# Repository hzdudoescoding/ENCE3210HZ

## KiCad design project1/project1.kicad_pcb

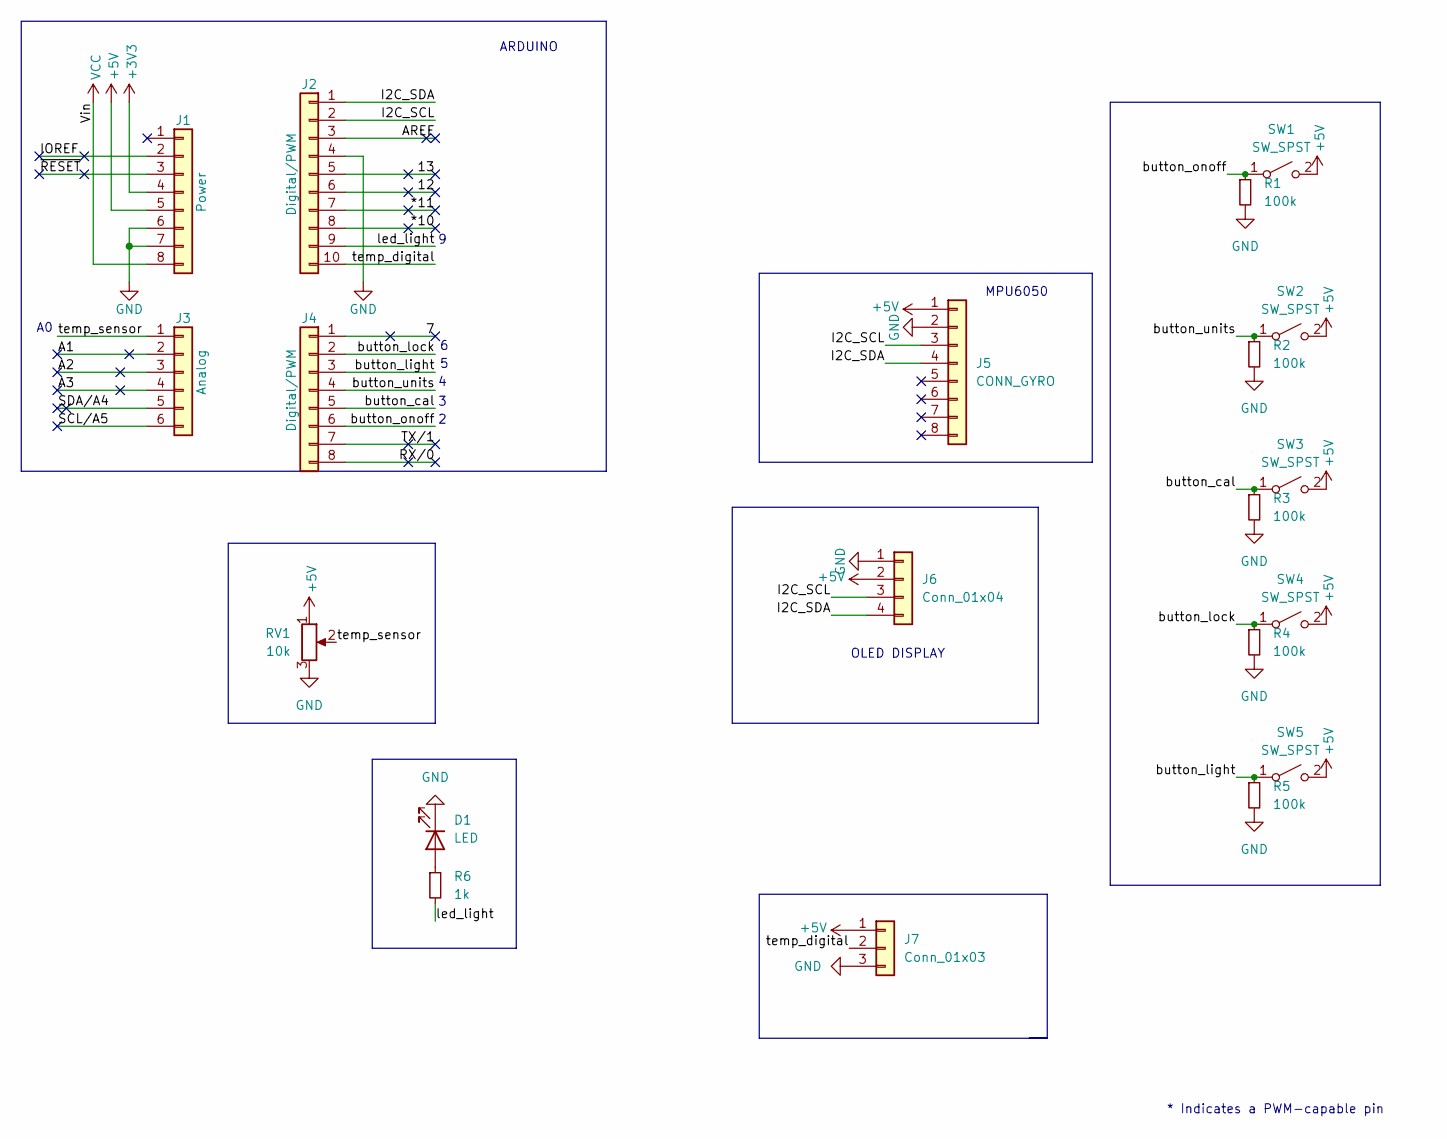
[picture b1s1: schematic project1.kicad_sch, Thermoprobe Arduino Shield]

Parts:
D1: LED; LED_D5.0mm
J1: Power; PinSocket_1x08_P2.54mm_Vertical
J2: Digital/PWM; PinSocket_1x10_P2.54mm_Vertical
J3: Analog; PinSocket_1x06_P2.54mm_Vertical
J4: Digital/PWM; PinSocket_1x08_P2.54mm_Vertical
J5: CONN_GYRO; PinSocket_1x08_P2.54mm_Vertical
J6: Conn_01x04; PinSocket_1x04_P2.54mm_Vertical
J7: Conn_01x03; JST_XH_B3B-XH-A_1x03_P2.50mm_Vertical
R1, R2, R3, R4, R5: 100k; R_Axial_DIN0207_L6.3mm_D2.5mm_P10.16mm_Horizontal
R6: 1k; R_Axial_DIN0207_L6.3mm_D2.5mm_P10.16mm_Horizontal
RV1: 10k; Potentiometer_Bourns_3386P_Vertical
SW1, SW2, SW3, SW4, SW5: SW_SPST; SW_PUSH_6mm

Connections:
+3V3: J1.4
+5V: J1.5, J5.1, J6.2, J7.1, RV1.1, SW1.2 (B), SW2.2 (B), SW3.2 (B), SW4.2 (B), SW5.2 (B)
/7: J4.1
/12: J2.6
/13: J2.5
/*10: J2.8
/*11: J2.7
/A1: J3.2
/A2: J3.3
/A3: J3.4
/AREF: J2.3
/I2C_SCL: J2.2, J5.3, J6.3
/I2C_SDA: J2.1, J5.4, J6.4
/IOREF: J1.2
/RX/0: J4.8
/SCL/A5: J3.6
/SDA/A4: J3.5
/TX/1: J4.7
/button_cal: J4.5, R3.1, SW3.1 (A)
/button_light: J4.3, R5.1, SW5.1 (A)
/button_lock: J4.2, R4.1, SW4.1 (A)
/button_onoff: J4.6, R1.1, SW1.1 (A)
/button_units: J4.4, R2.1, SW2.1 (A)
/led_light: J2.9, R6.2
/temp_digital: J2.10, J7.2
/temp_sensor: J3.1, RV1.2
/~RESET: J1.3
GND: D1.1 (K), J1.6, J1.7, J2.4, J5.2, J6.1, J7.3, R1.2, R2.2, R3.2, R4.2, R5.2, RV1.3
unnamed: D1.2 (A), R6.1
VCC: J1.8

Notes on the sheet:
OLED DISPLAY
ARDUINO
MPU6050
* Indicates a PWM-capable pin

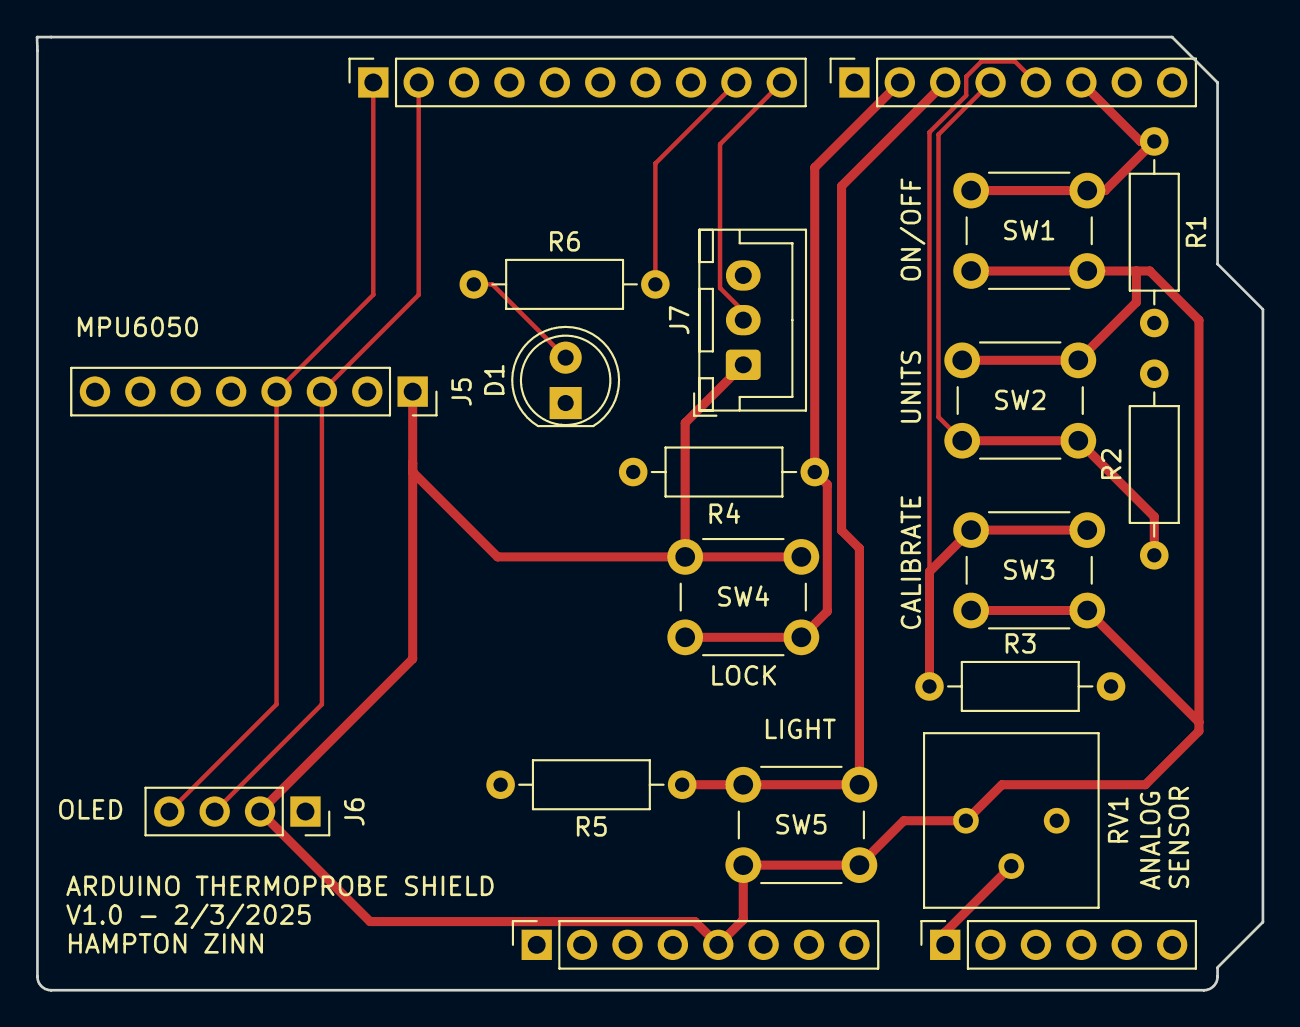
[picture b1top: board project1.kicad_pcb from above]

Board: 2 copper layers, 68.6 x 53.3 mm, 20 parts (0 on the bottom side), 13 nets.
